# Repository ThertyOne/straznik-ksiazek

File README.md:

# Strażnik książek – Mechatroniczny Trzymacz Książek

Projekt realizowany w ramach kursu **Systemy elektroniczne w mechatronice** na Politechnice Wrocławskiej.

## 📚 Opis projektu

**Strażnik książek** to inteligentny trzymacz książek w formie figurki Iron-Mana, który reaguje na obecność użytkownika oraz warunki otoczenia. Urządzenie integruje różne technologie mechatroniczne, takie jak:

- Wykrywanie ruchu (czujnik PIR)
- Detekcja obecności książek (fotorezystor)
- Pomiar światła dziennego (fotorezystor)
- Podświetlenie LED (WS2812)
- Ruchoma głowa figurki (serwo MG90S)
- Efekty dźwiękowe (DFPlayer Mini + głośnik)

## ⚙️ Wykorzystane komponenty

- **Mikrokontroler**: Arduino Nano V3.0  
- **Czujniki**: PIR HC-SR505, 2x fotorezystor GL5616  
- **Wykonawcze**: serwomechanizm MG90S, listwa LED WS2812 (2x po 8 diod)  
- **Dźwięk**: DFPlayer Mini + głośnik 1W 8Ω  
- **Zasilanie**: 5V/2A (gniazdo DC barrel)  

## 💡 Funkcjonalność

1. Detekcja ruchu użytkownika aktywuje system.
2. Sprawdzana jest obecność książek oraz poziom światła dziennego.
3. Jeśli książki są obecne i jest ciemno:
   - Włączane jest podświetlenie LED.
   - Głowa figurki porusza się w stronę użytkownika.
   - Odtwarzany jest losowy dźwięk Iron-Mana (MP3 z karty SD).

System automatycznie się dezaktywuje przy braku ruchu.

## 🧠 Kod i biblioteki

Kod Arduino wykorzystuje następujące biblioteki:

- `Servo.h` – sterowanie serwem  
- `Adafruit_NeoPixel.h` – sterowanie LED WS2812  
- `SoftwareSerial.h` – komunikacja z DFPlayer Mini  
- `DFRobotDFPlayerMini.h` – obsługa odtwarzacza MP3

## 📦 Zawartość repozytorium

- `kod.ino` – kod źródłowy dla Arduino
- `schematy/` – schematy elektroniczne (.sch, .brd)
- `3d/` – modele 3D (.stl, .step)
- `bom.csv` – lista komponentów (Bill of Materials)
- `dokumentacja.pdf` – pełna dokumentacja projektowa
- `rysunki_złożeniowe.pdf` – wizualizacje montażu

## 👤 Autor

**Dominik Bukowicz**

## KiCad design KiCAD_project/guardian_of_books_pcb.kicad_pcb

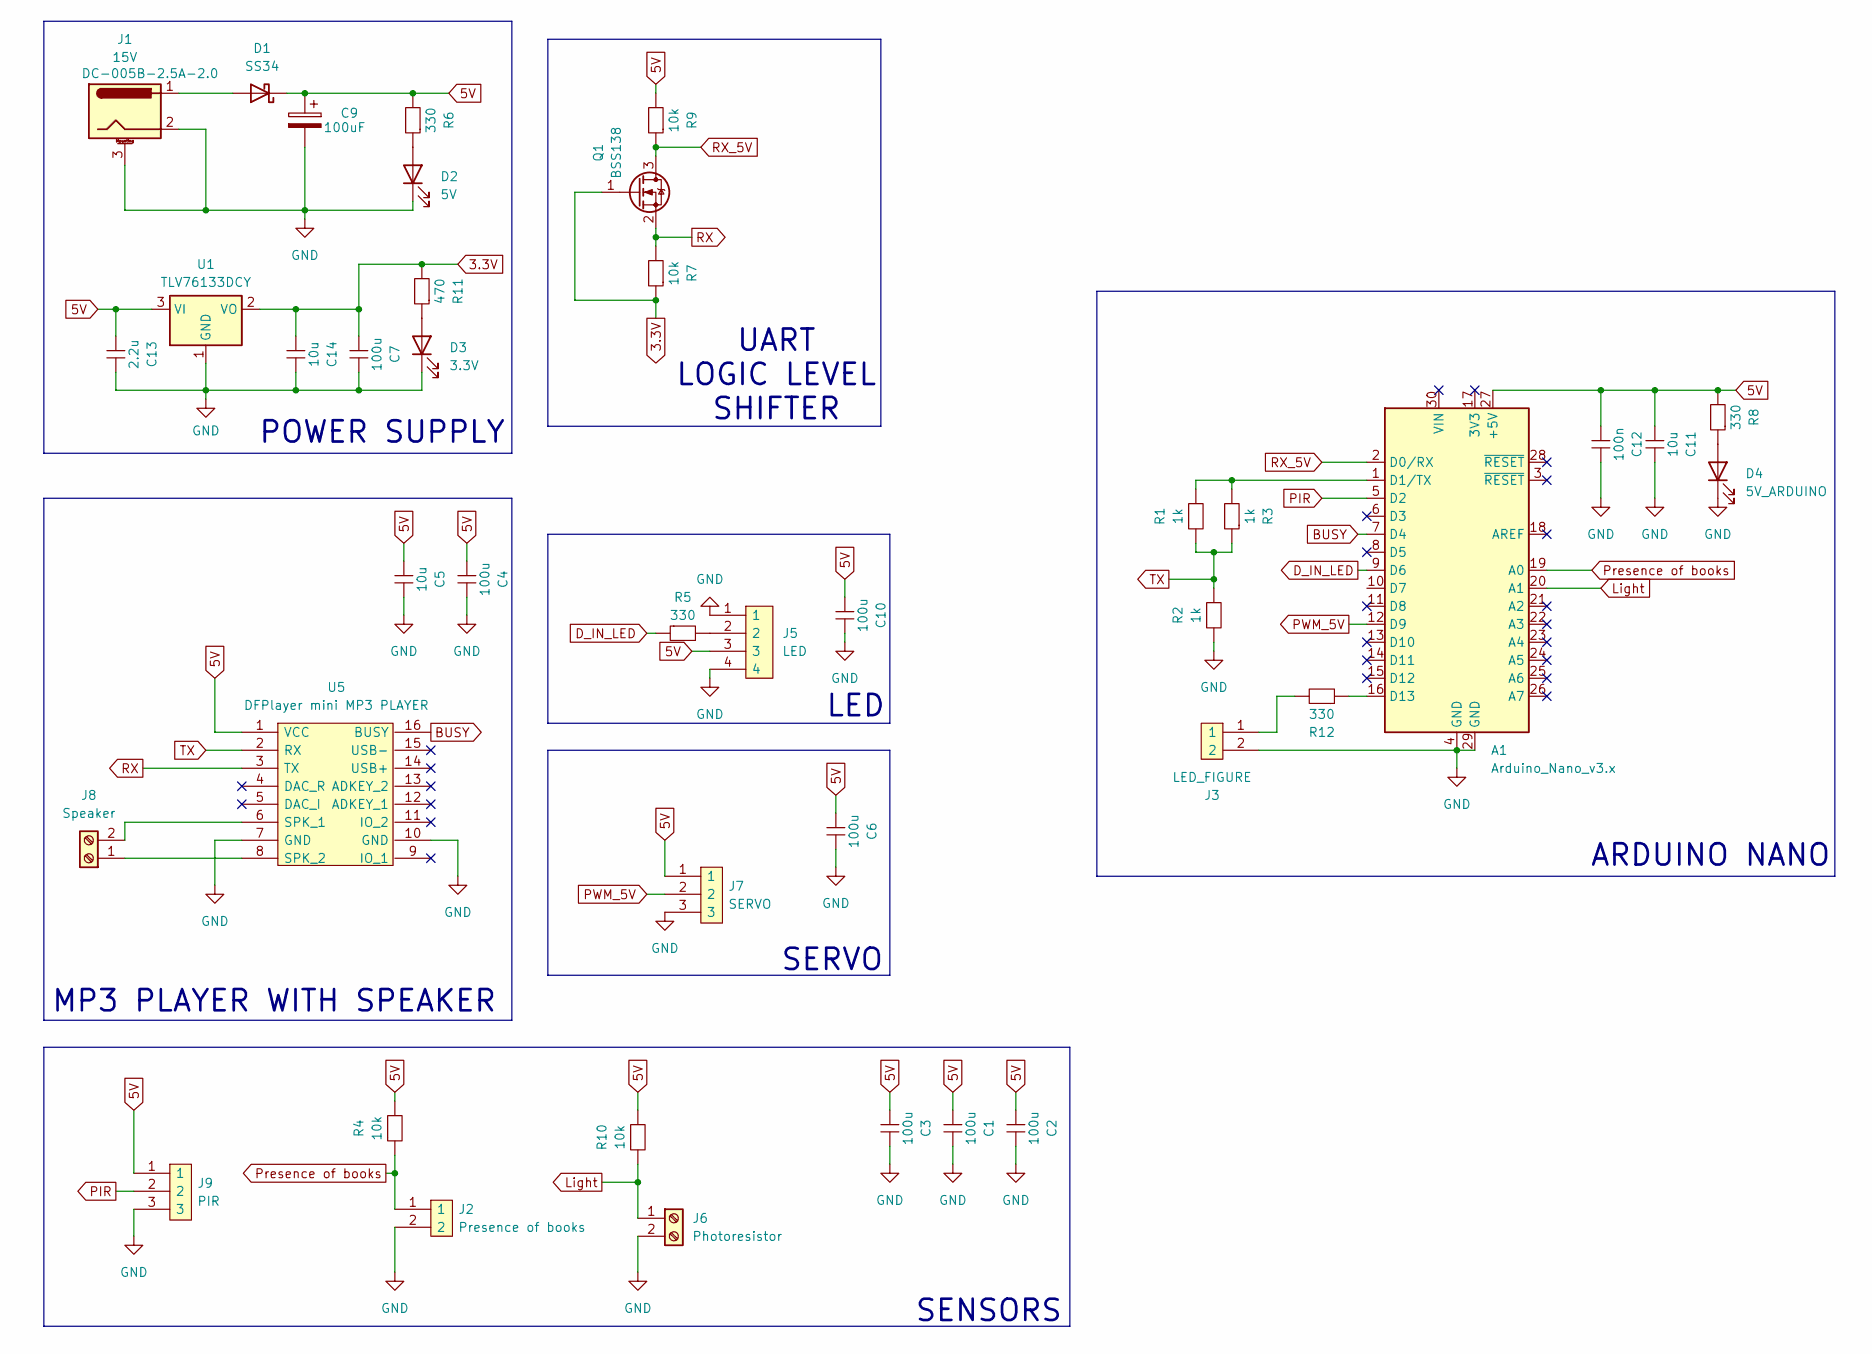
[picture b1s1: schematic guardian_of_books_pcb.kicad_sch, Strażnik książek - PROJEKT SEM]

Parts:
A1: Arduino_Nano_v3.x; Arduino_Nano
C1, C2, C3, C4, C6, C7, C10: 100u; cap_0603
C5, C11, C14: 10u; cap_0603
C9: 100uF; CP_Elec_6.3x7.7
C12: 100n; cap_0603
C13: 2.2u; cap_0603
D1: SS34; D_SMA
D2: 5V; LED_SMD
D3: 3.3V; LED_SMD
D4: 5V_ARDUINO; LED_SMD
J1: 15V; BarrelJack_Horizontal
J2: Presence of books; pin_con_2_female; Mouser Part Number 710-61300811821
J3: LED_FIGURE; pin_con_2_female; Mouser Part Number 710-61300811821
J5: LED; pin_con_4_female; Mouser Part Number 710-61300811821
J6: Photoresistor; screw_conector
J7: SERVO; pin_con_e_female; Mouser Part Number 710-61300811821
J8: Speaker; screw_conector
J9: PIR; pin_con_e_female; Mouser Part Number 710-61300811821
Q1: BSS138; SOT-23
R1, R2, R3: 1k; res_0603
R4, R7, R9, R10: 10k; res_0603
R5, R6, R8, R12: 330; res_0603
R11: 470; res_0603
U1: TLV76133DCY; SOT-223-3_TabPin2
U5: DFPlayer mini MP3 PLAYER; Mouser Part Number 710-61300811821

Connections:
3.3V: C7.1, C14.1, Q1.1 (G), R7.1, R11.2, U1.2 (VO)
5V: A1.27 (+5V), C1.1, C2.1, C3.1, C4.1, C5.1, C6.1, C9.1, C10.1, C11.1, C12.1, C13.1, D1.1 (K), J5.3, J7.1, J9.1, R4.2, R6.2, R8.2, R9.2, R10.2, U1.3 (VI), U5.1 (VCC)
BUSY: A1.7 (D4), U5.16 (BUSY)
D_IN_LED: A1.9 (D6), R5.1
GND: A1.4 (GND), A1.29 (GND), C1.2, C2.2, C3.2, C4.2, C5.2, C6.2, C7.2, C9.2, C10.2, C11.2, C12.2, C13.2, C14.2, D2.1 (K), D3.1 (K), D4.1 (K), J1.2, J1.3 (MountPin), J2.2, J3.2, J5.1, J5.4, J6.2, J7.3, J9.3, R2.1, U1.1 (GND), U5.7 (GND), U5.10 (GND)
Light: A1.20 (A1), J6.1, R10.1
unnamed: A1.1 (D1/TX), R1.2, R3.2
unnamed: A1.16 (D13), R12.1
unnamed: D1.2 (A), J1.1
unnamed: D2.2 (A), R6.1
unnamed: D3.2 (A), R11.1
unnamed: D4.2 (A), R8.1
unnamed: J3.1, R12.2
unnamed: J5.2, R5.2
unnamed: J8.1, U5.8 (SPK_2)
unnamed: J8.2, U5.6 (SPK_1)
PIR: A1.5 (D2), J9.2
PWM_5V: A1.12 (D9), J7.2
Presence of books: A1.19 (A0), J2.1, R4.1
RX: Q1.2 (S), R7.2, U5.3 (TX)
RX_5V: A1.2 (D0/RX), Q1.3 (D), R9.1
TX: R1.1, R2.2, R3.1, U5.2 (RX)

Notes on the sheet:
MP3 PLAYER WITH SPEAKER
LED
ARDUINO NANO
SERVO
SENSORS
POWER SUPPLY
UART LOGIC LEVEL SHIFTER

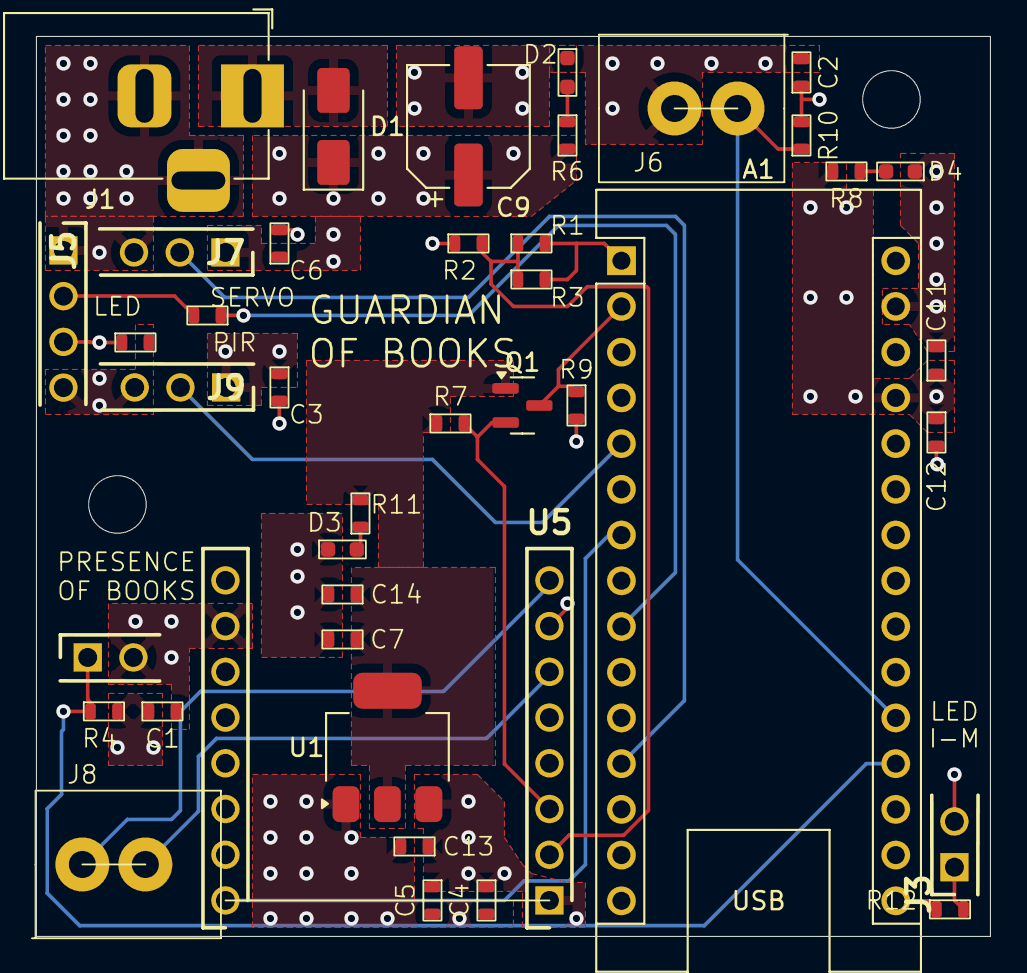
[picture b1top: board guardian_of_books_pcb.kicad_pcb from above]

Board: 4 copper layers, 53.0 x 50.0 mm, 41 parts (0 on the bottom side), 22 nets.

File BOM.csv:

Nr.;Oznaczenie;Footprint;Ilo??;Nazwa / numer seryjny;Warto??;Tolerancja;Cena za szt. [z?];URL;;;
1;R11;res_0603;1;RC0603FR-07470RP;470;±1%;0,39;https://www.digikey.pl/pl/products/detail/yageo/RC0603FR-074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;;;
2;R12,R6,R5,R8;res_0603;4;RC0603JR-13330RL;330;±5%;0,39;https://www.digikey.pl/pl/products/detail/yageo/RC0603JR-133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;;;
3;R1,R2,R3;res_0603;3;RC0603FR-131KL;1k;±1%;0,39;https://www.digikey.pl/pl/products/detail/yageo/RC0603FR-131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;;;
4;R4,R9,R10,R7;res_0603;4;RC0603FR-13330KL;10k;±1%;0,39;https://www.digikey.pl/pl/products/detail/yageo/RC0603FR-133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;;;
5;C6,C4,C3,C1,C7,C2,C10;cap_0603;7;GRM31CR60J107KEA8L;100u;±10%;0,46;https://www.digikey.com/en/products/detail/murata-electronic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;;;
6;C13;cap_0603;1;C0603C225K4PACTU;2.2u;±10%;0,47;https://www.digikey.pl/pl/products/detail/kemet/C0603C225K4P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;;;
7;C11,C14,C5;cap_0603;3;;10u;±20%;1,6;https://www.mouser.pl/ProductDetail/TDK/C1608X5R1E106M080AC?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;;;
8;C12;cap_0603;1;C0603C104M5REC7411;100n;±20%;0,53;https://www.mouser.pl/ProductDetail/KEMET/C0603C104M5REC7411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;;;
9;C9;CP_Elec_6.3x7.7;1;EEE-FN1V101XP;100uF;±20%;2,45;https://www.mouser.pl/ProductDetail/Panasonic/EEE-FN1V101XP?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;;;
10;D1;D_SMA;1;;SS34;;4,45;https://www.tme.eu/en/details/ss34-cdi/smd-schottky-diodes/c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;;;
11;D2, D3, D4;LED_SMD;3;;5V;;3,21;https://www.tme.eu/pl/details/of-smd2012g/diody-led-smd-kolo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;;;
12;J1;BarrelJack_Horizontal;1;PJ-102B;15V;;2,29;https://www.mouser.pl/ProductDetail/Same-Sky/PJ-102B?qs=Wyjl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;;;
13;J2, J3, J5, J7, J9, U5;pin_con_10_female;3;;;;4,52;https://www.mouser.pl/ProductDetail/Harwin/M20-7820646?qs=WS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;;;
14;J8, J6;screw_conector;2;Listwa zaciskowa;;;1,85;https://www.tme.eu/pl/details/282837-2/listwy-zaciskowe-do-d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;;;
15;U1;SOT-223-3_TabPin2;1;TLV76133DCY;;;1,59;https://www.digikey.pl/en/products/detail/texas-instruments/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;;;
16;Q1;SOT-23;1;BSS138;;;0,97;https://www.tme.eu/pl/details/bss138wh6327xtsa1/tranzystory-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;;;
17;-;DFPlayer Mini;1;DFPlayer Mini;;;27,9;https://botland.com.pl/odtwarzacze-mp3-wav-ogg-midi/3170-dfp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;;;
18;A1;Arduino_Nano;1;Arduino_Nano_v3.x;;;19,9;https://sklep.msalamon.pl/produkt/nano-v3-0-z-usb-c-zgodny-z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;;;
19;-;servo;1;MG-90 - micro - 180;;;17,9;https://botland.com.pl/serwa-typu-micro/20436-serwo-mg-90s-m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;;;
20;-;listwa LED;2;LED RGB WS2812 5050 x 8 diod - 53mm;;;15,9;https://botland.com.pl/lancuchy-i-matryce-led/6255-listwa-le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;;;
21;-;glosnik 8 Ohm;1;G?o?nik 1 W 8 Ohm;;;11,9;https://botland.com.pl/czujniki-ruchu/5862-czujnik-ruchu-min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;;;
22;-;fotorezystor;2;Fotorezystor 5-10k? GL5616;;;4,9;https://botland.com.pl/glosniki-analogowe/19458-glosnik-1w-8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;;;
23;-;PIR;1;mini PIR HC-SR505;;;9,9;https://botland.com.pl/czujniki-ruchu/5862-czujnik-ruchu-min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;;;
24;-;zasilacz;1;Zasialacz 5V 2A - DC barrle;;;26,9;https://botland.com.pl/zasilacze-dogniazdkowe/4088-zasilacz-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;;;
25;-;gwinty insert do monta?u;1;Inserty gwintowe ró?ne rodzaje (M2, M3, M6);;;22,9;https://botland.com.pl/pozostale-akcesoria-do-drukrek-3d/220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;;;
26;-;sruby ;;?ruby monta?owe M3, M6;;;49;https://botland.com.pl/srubki-i-nakretki/23456-zestaw-srub-i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;;;
27;-;sruby ;;?ruby monta?owe M2, M3;;;11,9;https://botland.com.pl/srubki-i-nakretki/637-zestaw-srubek-p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;;;
28;-;plexy matowe;;P?yta plexy matowa;;;49;https://botland.com.pl/materialy-do-obrobki/20912-plexi-mlec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;;;
29;-;plexy przezroczyste;;P?yta plexy przezroczysta;;;59,9;https://botland.com.pl/materialy-do-obrobki/20909-plexi-prze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;;;
30;-;klej;1;Klej do mocowania p?yt;;;4,5;https://botland.com.pl/kleje-i-klejarki/1367-klej-kropelka-2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;;;
;;;;;;;;;;;
;;;;;;SUMA;358,35;;;;

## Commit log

2025-04-15 first
